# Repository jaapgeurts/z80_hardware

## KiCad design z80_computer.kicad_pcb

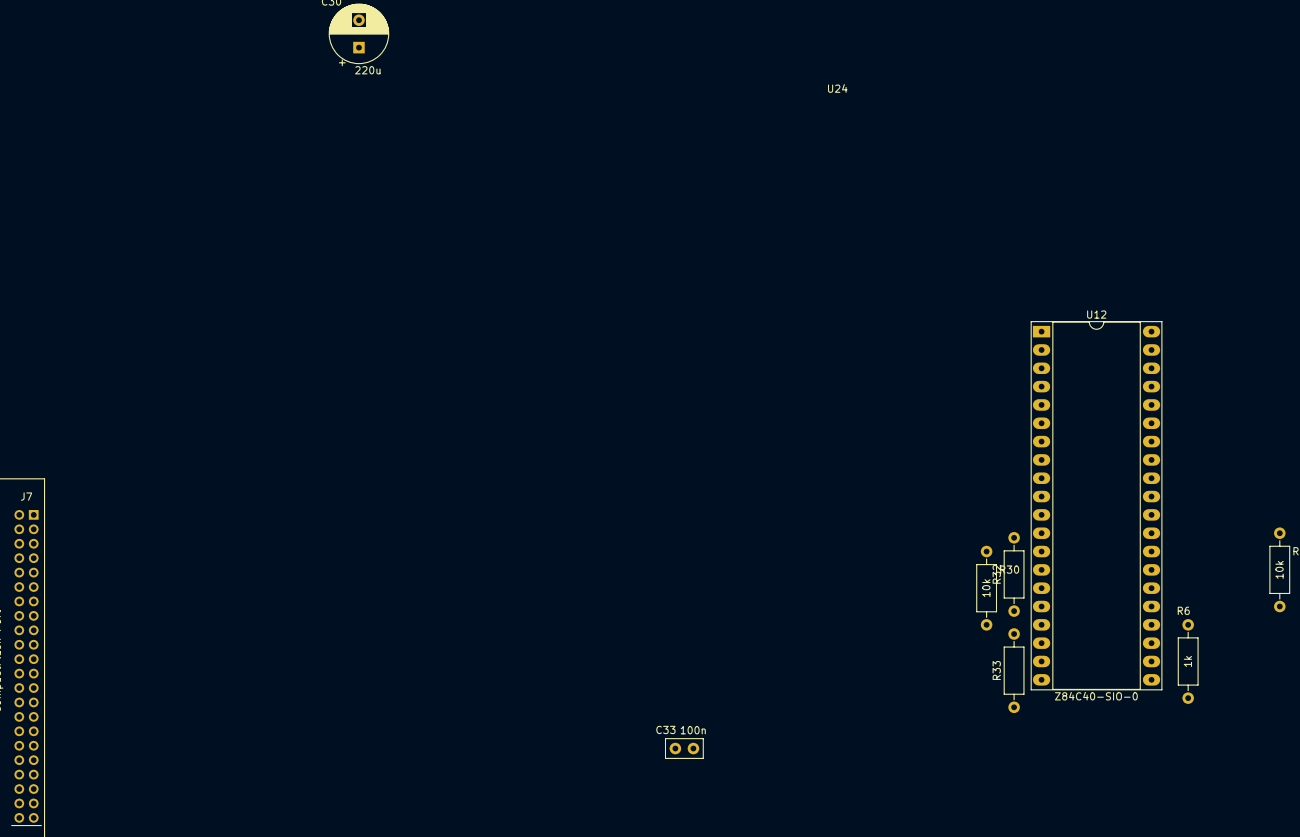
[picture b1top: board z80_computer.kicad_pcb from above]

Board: 2 copper layers, 13 parts (0 on the bottom side), 19 nets, no tracks yet.

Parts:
C30: 220u; CP_Radial_D8.0mm_P3.80mm
C33: 100n; C_Disc_D5.0mm_W2.5mm_P2.50mm
H5: PlaceHolder Sea80; wave_logo
H6: PlaceHolder for OS Hardware; OSHW-Logo_19x20mm_SilkScreen
H7: Placeholder Graphic; Symbol_Barrel_Polarity
J7: CompactFlash Port; CompactFlash_Module
R6: 1k; R_Axial_DIN0207_L6.3mm_D2.5mm_P10.16mm_Horizontal
R30, R31: 10k; R_Axial_DIN0207_L6.3mm_D2.5mm_P10.16mm_Horizontal
R32, R33: 2k7; R_Axial_DIN0207_L6.3mm_D2.5mm_P10.16mm_Horizontal
U12: Z84C40-SIO-0; DIP-40_W15.24mm_Socket_LongPads
U24: OPEN-SMART-3.5; OPENSMART-3.5in-LCD

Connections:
+5V: C33.1, J7.41, J7.42, R6.1, R30.1, R31.1, U12.6, U12.9
/Input Output/RxTxCA: U12.13, U12.14
A0: J7.35, U12.34
A1: J7.33, U12.33
D0: J7.17, U12.40
D1: J7.15, U12.1
D2: J7.13, U12.39
D3: J7.11, U12.2
D4: J7.9, U12.38
D5: J7.7, U12.3
D6: J7.5, U12.37
D7: J7.3, U12.4
GND: C33.2, J7.2, J7.19, J7.22, J7.24, J7.26, J7.30, J7.40, J7.43, U12.31
unnamed: R30.2, U12.11
unnamed: R31.2, U12.29
unnamed: R32.2, U12.12
unnamed: R33.2, U12.15
~RD: J7.25, U12.32
~RESET: J7.1, R6.2, U12.21

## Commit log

2021-02-02 PCB rev1 breadboard version
2021-02-04 Monitor now supports loading from serial, dumping data and running loaded data schematic updates
2021-02-05 Added basic support for PS/2 keyboard - in code and schematic
2021-02-15 Saving language progress
2021-02-17 Added test cases; merging eval expression and ident/literal
2021-02-17 Before adding arrays. Started writing rom in R8
2021-02-20 Function parameters now correctly assigned to registers
2021-02-21 Initial assembly code works. Converting firmware from asm to retro8
2021-02-22 r8 strcmp() and readline() version working
2021-02-22 My own readline() now working for real
2021-02-22 Added port in,out syntax
2021-02-23 Constants are commited to assembly now
2021-02-23 Fixed bugs and string escape sequence now converted
2021-02-24 Added unittest for toAsmStr
2021-02-26 Fixed bugs. Added elif block to if statement
2021-02-26 Bug fixes
2021-02-28 Fixed comparison expressions
2021-03-02 Bug fixes, interrupts mode 1 working and added files
2021-03-03 Merged keyboard code
2021-03-03 Split off into schematic
2021-03-04 Added changes to CTC
2021-03-05 Added RTC
2021-03-07 Added PIO to schematic
2021-03-10 Added PSG audio output stage
2021-03-11 Added circuit for PS/2 host-device communication
2021-03-17 Added expansion bus and GPIO ports
2021-03-17 Updated schematic
2021-03-19 All footprints assigned
2021-03-19 Renamed sound sheet
2021-03-19 Removed old soundio
2021-03-21 PCB tracing done
2021-03-21 PCB pwr connected
2021-03-21 Fixed up issues
2021-03-22 Fine tuned board traces
2021-03-22 Added two pullups to SIO/SYNC
2021-04-05 Added schematic pdf. small bugfixes
2021-04-05 Updating PCB. moving ram to middle, IO to lower part
2021-04-07 Board rerouted. Missing Creative commons
2021-04-12 Revision 2 bug fix. NMI / INT reversed. Added resistors to UART Rx/Tx
2021-05-04 buf fixes
2021-05-04 Bug fixes. Moved components two new sheet; added voltage monitor for RTC
2021-05-17 Added RTC voltage detection circuit
2021-05-20 Renamed
2021-05-27 Moved schematic into correct folder
2021-05-27 Moved schematic to REV2 folder
